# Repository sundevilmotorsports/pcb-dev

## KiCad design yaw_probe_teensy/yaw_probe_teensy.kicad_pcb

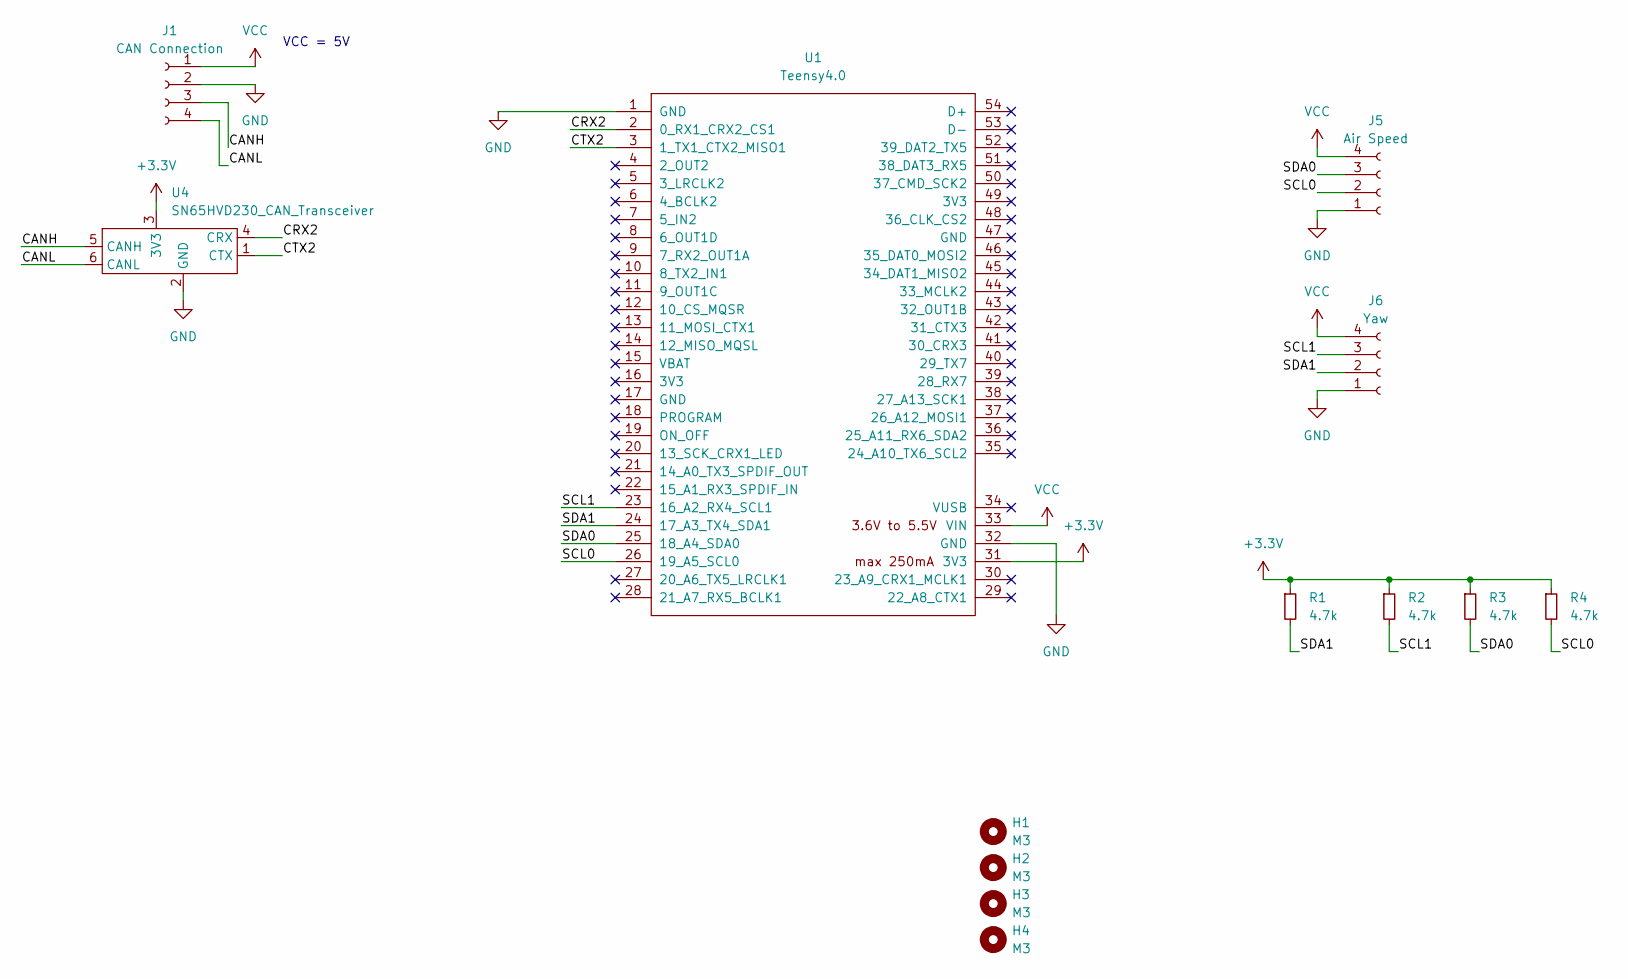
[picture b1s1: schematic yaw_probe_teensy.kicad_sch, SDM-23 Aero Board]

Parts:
H1, H2, H3, H4: M3; MountingHole_3.2mm_M3
J1: CAN Connection; TerminalBlock_TE_282834-4_1x04_P2.54mm_Horizontal
J5: Air Speed; TerminalBlock_TE_282834-4_1x04_P2.54mm_Horizontal
J6: Yaw; TerminalBlock_TE_282834-4_1x04_P2.54mm_Horizontal
R1, R2, R3, R4: 4.7k; R_Axial_DIN0207_L6.3mm_D2.5mm_P7.62mm_Horizontal
U1: Teensy4.0; Teensy40
U4: SN65HVD230_CAN_Transceiver; SDM_CANBoard_v1

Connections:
+3.3V: R1.1, R2.1, R3.1, R4.1, U1.31 (3V3), U4.3 (3V3)
/CANH: J1.3, U4.5 (CANH)
/CANL: J1.4, U4.6 (CANL)
/CRX2: U1.2 (0_RX1_CRX2_CS1), U4.4 (CRX)
/CTX2: U1.3 (1_TX1_CTX2_MISO1), U4.1 (CTX)
/SCL0: J5.2, R4.2, U1.26 (19_A5_SCL0)
/SCL1: J6.3, R2.2, U1.23 (16_A2_RX4_SCL1)
/SDA0: J5.3, R3.2, U1.25 (18_A4_SDA0)
/SDA1: J6.2, R1.2, U1.24 (17_A3_TX4_SDA1)
GND: J1.2, J5.1, J6.1, U1.1 (GND), U1.32 (GND), U4.2 (GND)
VCC: J1.1, J5.4, J6.4, U1.33 (VIN)

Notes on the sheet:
VCC = 5V

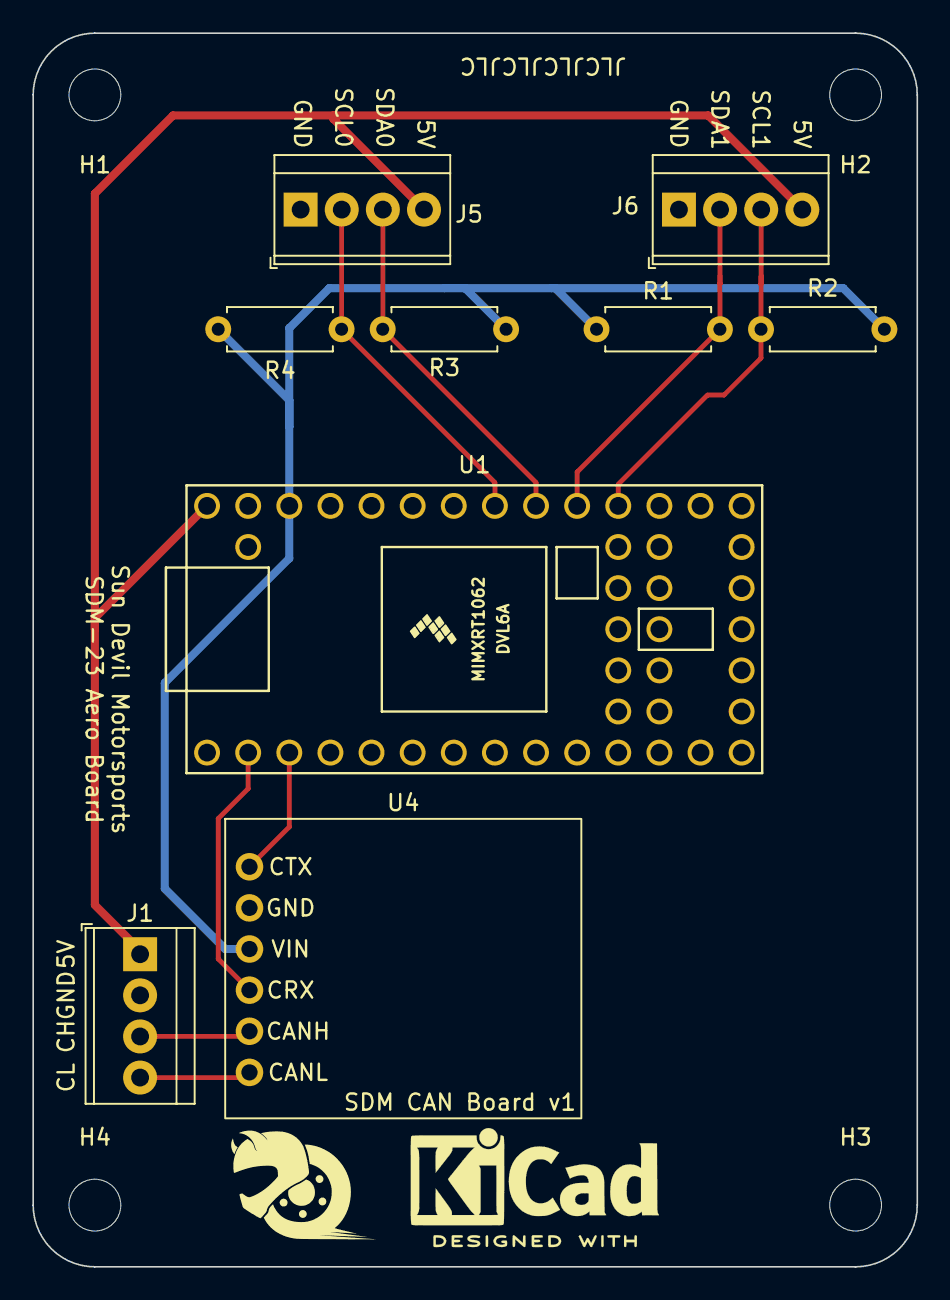
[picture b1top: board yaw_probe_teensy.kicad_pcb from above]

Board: 2 copper layers, 54.6 x 76.2 mm, 13 parts (0 on the bottom side), 11 nets.
